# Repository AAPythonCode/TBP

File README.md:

# TBP (Tennis Ball Picker)

Hey!

Check out my JOURNALS.MD [here](https://github.com/AAPythonCode/TBP/blob/main/JOURNALS.md)

It's summer break, and I want to create something cool! Since I play tennis on a daily basis, I thought of creating something related to it. Therefore, I thought of creating a tennis ball picker that could collect tennis balls for the user, without collecting other players'.

I brainstormed many ideas, but in the end I thought of using cones on each of the four corners of the court to track the bot. Each cone would have a DWM1000 and a ESP32-WROOM-32, a low-cost programmable chip. The bot would also have the same, slightly modified board, which would use the distance data from each of the cones to find where it would be in relation to them.

Here's a drawing I made (painfully, my hand was shaking lol, did this on a phone):

# Bill of Materials (BOM)

### LCSC BOM:
| # | LCSC Part # | MPN | Manufacturer | Package | Quantity | Description |
|---:|-------------|-----|--------------|---------|---------:|-------------|
| 1 | C5241969 | DW1000-I-TR13 | Qorvo | QFN-48 (6×6 mm) | 5 | RF Transceiver IC, 3.244–6.999 GHz, 6.8 Mbps, −107 dBm, 2.8–3.6 V |
| 2 | C2907044 | FRC0603F5101TS | FOJAN | 0603 | 100 | 5.1 kΩ ±1%, 100 mW Thick Film Resistor |
| 3 | C717453 | S8050 | LGE | TO-92 | 20 | NPN BJT Transistor, 25 V, 500 mA, 150 MHz |
| 4 | C19273151 | YLED0603G | YONGYUTAI | 0603 | 100 | Emerald Green Indicator LED, 2.7–3.2 V |
| 5 | C141517 | TB6612FNG,C,8,EL | Toshiba | SSOP-24 | 1 | Dual H-Bridge Motor Driver |
| 6 | C695629 | DB301V-3.5-2P-GN-S | DORABO | Through Hole, 3.5 mm Pitch | 5 | 2-Position Wire-to-Board Terminal Block |
| 7 | C91606 | GRM188R61E106MA73D | Murata | 0603 | 5 | 10 µF ±20%, 25 V X5R Ceramic Capacitor |
| 8 | C2762594 | CL10A226MO7JZNC | Samsung Electro-Mechanics | 0603 | 5 | 22 µF ±20%, 16 V X5R Ceramic Capacitor |
| 9 | C207830 | SLO0420H4R7MTT | Sunltech | 4.2 × 4.2 mm SMD | 5 | 4.7 µH Molded Inductor, 2.2 A, 84 mΩ |
| 10 | C1590 | CL10B104KA8NNNC | Samsung Electro-Mechanics | 0603 | 50 | 100 nF ±10%, 25 V X7R Ceramic Capacitor |
| 11 | C98220 | RC0603FR-0710KL | YAGEO | 0603 | 100 | 10 kΩ ±1%, 100 mW Thick Film Resistor |
| 12 | C328062 | ESP32-WROOM-32U-N4 | Espressif | SMD, 19.2 × 18 mm | 5 | ESP32-WROOM-32U Wi-Fi/Bluetooth Module (External Antenna) |

## BOM For Everything Else:
| Product | Price | Manufacturer | Quantity | Link |
|---------|-------|--------------|----------|------|
Battery For Bot | $8.24 | AliExpress | 1 | [Link](https://www.aliexpress.us/item/3256811572811807.html?spm=a2g0o.detail.0.0.241ee2aYe2aY9A&mp=1&pdp_npi=6%40dis%21USD%21USD+31.69%21USD+8.20%21%21USD+8.20%21%21%21%40210327ef17836526403843839e1164%2112000056452625915%21ct%21US%21-1%21%211%210%21&_gl=1*mowjt7*_gcl_au*MTM5NjU0MTYyNC4xNzgyMTg1MjIw*_ga*OTg3MTQ2MjQ4LjE3ODM2NDk2ODY.*_ga_VED1YSGNC7*czE3ODM2NTE3ODgkbzIkZzEkdDE3ODM2NTI2MTckajU5JGwwJGgw&gatewayAdapt=glo2usa)
Battery For Cone | $3.67 | AliExpress | 4 | [Link](https://www.aliexpress.us/item/3256807641231334.html?spm=a2g0o.cart.0.0.677e38dazvj0aC&mp=1&pdp_npi=6%40dis%21USD%21USD+4.71%21USD+3.67%21%21USD+3.67%21%21%21%40210327ef17836529897426402e1164%2112000042353906286%21ct%21US%21-1%21%214%210%21&_gl=1*rah6qg*_gcl_au*MTM5NjU0MTYyNC4xNzgyMTg1MjIw*_ga*OTg3MTQ2MjQ4LjE3ODM2NDk2ODY.*_ga_VED1YSGNC7*czE3ODM2NTE3ODgkbzIkZzEkdDE3ODM2NTI5ODUkajQwJGwwJGgw&gatewayAdapt=glo2usa)
Caster Wheel (1 inch) | $6.89 | Amazon | 1 | [Link](https://www.amazon.com/Suiwotin-Casters-Replacement-Furniture-Cabinet/dp/B0C6JM7R2C/ref=sr_1_1?crid=G9WRSFY5IU30&dib=eyJ2IjoiMSJ9.7-JBT1HsoIndO6Nb_8mkSWVhn_iG1l5bbaN72kEroFq0E59IKfvyAlzAbGhL28Qy0klFiTsaZ9NMhDen2mC3Amcu-PpbKVTANfx0Uxh-y3oR3J0IiuYsMEy8AlGZf1hDu7_Nkn3xwIBqfYD3LpzfmKYA78j-cPIgqK75zkbXJZtpSlZKJ1o28_MMSl6raOjAua3VqijRvSrvi3kahNN8uuCBq-4MeWqScNZLNkaJBLk.mjZqq4LFhEt1wzEfHjUGeLU96UFfIbHFmp24r8qmJlg&dib_tag=se&keywords=caster%2Bwheel%2B2inch%2Bfor%2Bfurniture%2Bplate%2Bmount%2B2%2Bpcs&nsdOptOutParam=true&qid=1783467828&refinements=p_36%3A-800&rnid=2661611011&sprefix=caster%2Bwheel%2B2inch%2Bfor%2Bfurniture%2Bplate%2Bmount%2B2%2Bpc%2Caps%2C195&sr=8-1&th=1)
Wheels | $8.99 | AliExpress | 1 | [Link](https://www.amazon.com/gp/product/B0C6JQ3SDV/ref=ox_sc_act_title_2?smid=A22NPL1KB8AOV0&psc=1)
Motors | $4.34 | Amazon | 4 | [Link](https://www.amazon.com/gp/product/B0GXY1Y1XM/ref=ox_sc_act_title_2?smid=A3PMRUDTUKMNJ1&psc=1&s=bazaar)
DWM1000 | $0.80 | Alibaba | 5 | [Link](https://www.alibaba.com/product-detail/Electronic-components-integrated-circuits-semiconductor-New_1601393696798.html?spm=a2756.trade-order-standard.0.0.e08265aaEoXY4F)
### GRAND TOTAL: $349.28

# Images

Now for some images! Take it all in... :)

## The Schematic

## The LED

## The DWM1000 + ESP32-WROOM-32 (from left to right, respectively.)

## Transistors

## The Full Bot PCB

## The Bot PCB in 3D

## The Full Cone PCB

## The Cone PCB in 3D

## The Fully Assembled Bot

## The Fully Assembled Cone

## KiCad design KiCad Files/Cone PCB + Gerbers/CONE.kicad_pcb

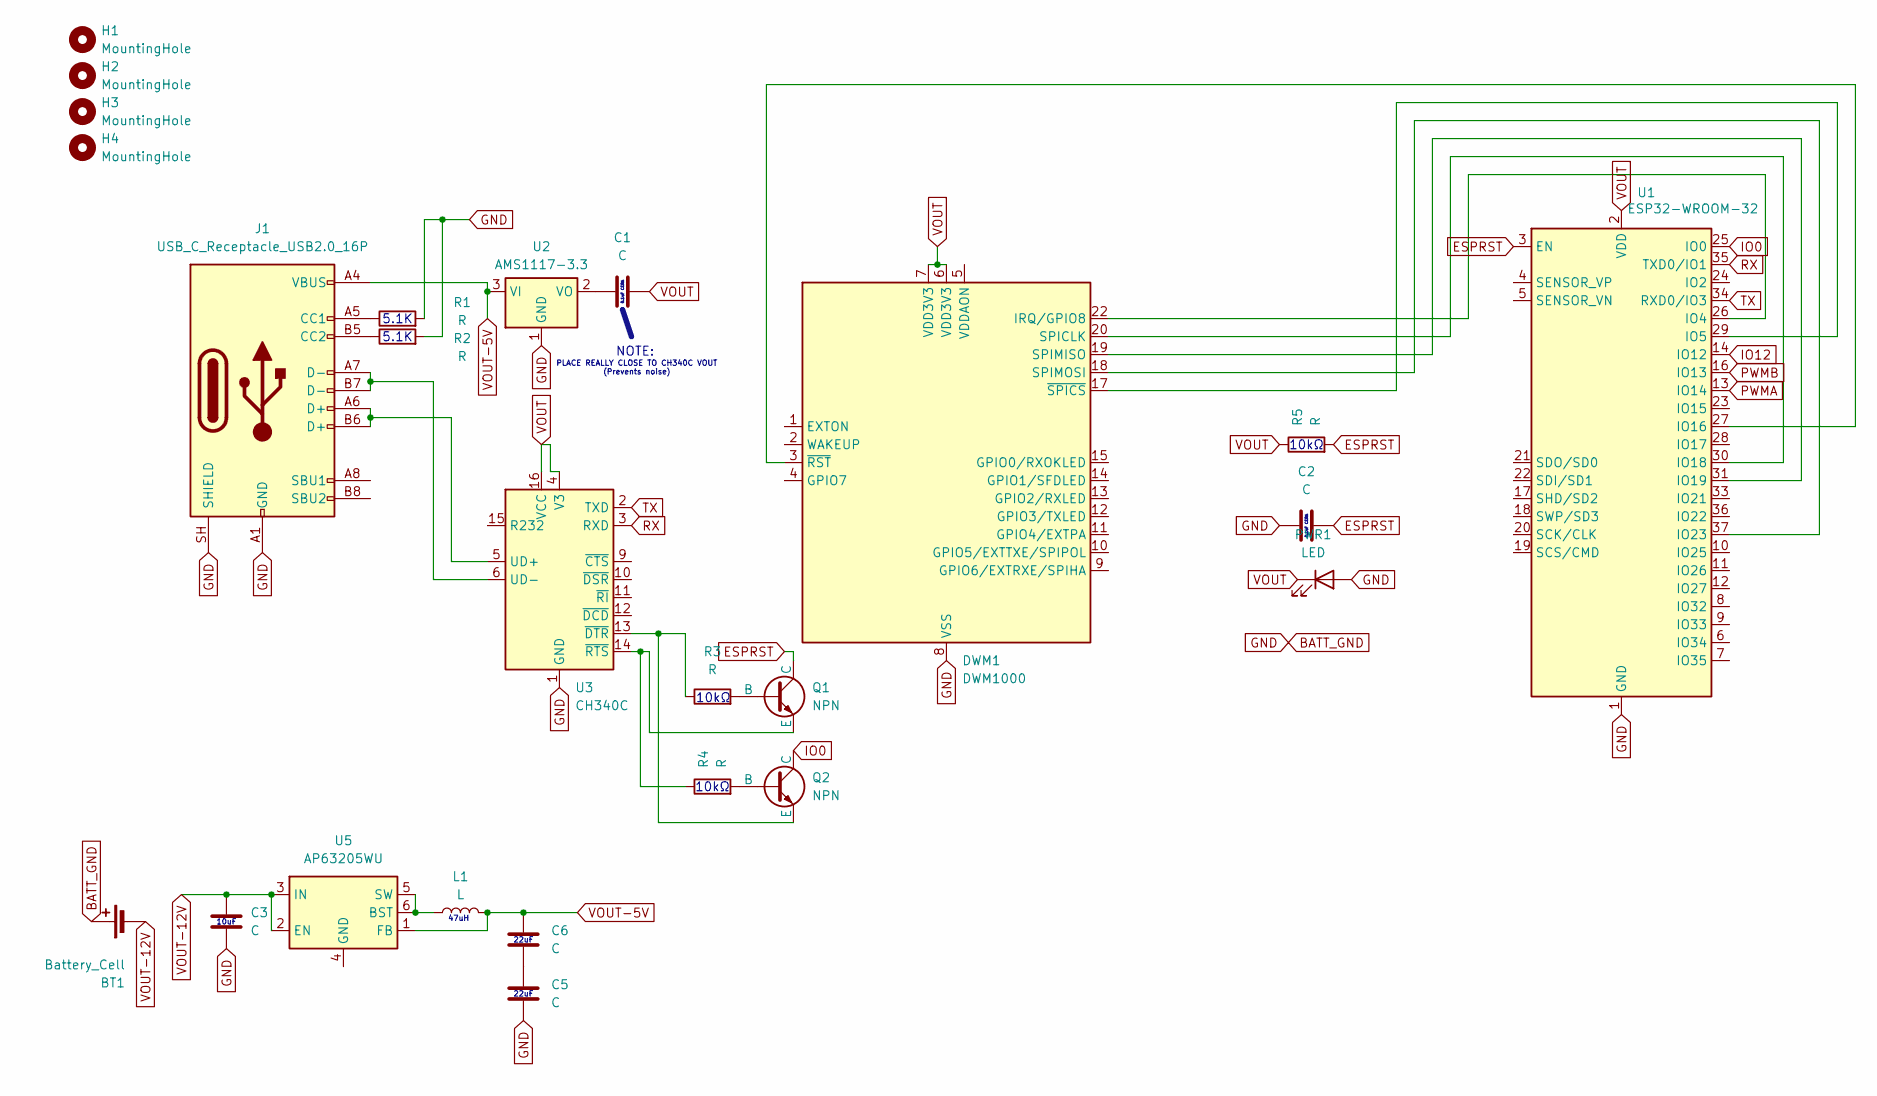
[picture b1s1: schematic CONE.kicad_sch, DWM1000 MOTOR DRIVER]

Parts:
BT1: Battery_Cell; PinSocket_1x02_P2.54mm_Vertical
C1, C2: C; C_0603_1608Metric
C3, C5, C6: C; C_0201_0603Metric
DWM1: DWM1000
H1, H2, H3, H4: MountingHole; MountingHole_2.5mm
J1: USB_C_Receptacle_USB2.0_16P; USB_C_Receptacle_HRO_TYPE-C-31-M-12
L1: L; IND_SRP4020TA-100M
PWR1: LED; LED_0603_1608Metric
Q1, Q2: NPN; TO-92
R1, R2, R3, R4, R5: R; R_0603_1608Metric
U1: ESP32-WROOM-32
U2: AMS1117-3.3; SOT-223-3_TabPin2
U3: CH340C; SOIC-16_3.9x9.9mm_P1.27mm
U5: AP63205WU; TSOT-23-6

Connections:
BATT_GND: BT1.1 (+), C2.1, C3.2, C5.2, DWM1.8 (VSS), DWM1.16 (VSS), DWM1.21 (VSS), DWM1.23 (VSS), DWM1.24 (VSS), J1.A1 (GND), J1.A12 (GND), J1.B1 (GND), J1.B12 (GND), J1.SH (SHIELD), PWR1.2 (A), R1.2, R2.2, U1.1 (GND), U1.15 (GND), U1.38 (GND), U1.39 (GND), U2.1 (GND), U3.1 (GND)
ESPRST: C2.2, Q1.1 (C), R5.2, U1.3 (EN)
IO0: Q2.1 (C), U1.25 (IO0)
IO12: U1.14 (IO12)
unnamed: C5.1, C6.2
unnamed: DWM1.22 (IRQ/GPIO8), U1.26 (IO4)
unnamed: DWM1.20 (SPICLK), U1.30 (IO18)
unnamed: DWM1.19 (SPIMISO), U1.31 (IO19)
unnamed: DWM1.18 (SPIMOSI), U1.37 (IO23)
unnamed: DWM1.3 (~RST), U1.27 (IO16)
unnamed: DWM1.17 (~SPICS), U1.29 (IO5)
unnamed: J1.A5 (CC1), R1.1
unnamed: J1.B5 (CC2), R2.1
unnamed: Q1.2 (B), R3.2
unnamed: Q1.3 (E), R4.1, U3.14 (~RTS)
unnamed: Q2.2 (B), R4.2
unnamed: Q2.3 (E), R3.1, U3.13 (~DTR)
unnamed: C1.1, U2.2 (VO)
unnamed: J1.A6 (D+), J1.B6 (D+), U3.5 (UD+)
unnamed: J1.A7 (D-), J1.B7 (D-), U3.6 (UD-)
unnamed: L1.1, U5.5 (SW), U5.6 (BST)
PWMA: U1.13 (IO14)
PWMB: U1.16 (IO13)
RX: U1.35 (TXD0/IO1), U3.3 (RXD)
TX: U1.34 (RXD0/IO3), U3.2 (TXD)
VOUT: C1.2, DWM1.6 (VDD3V3), DWM1.7 (VDD3V3), PWR1.1 (K), R5.1, U1.2 (VDD), U3.4 (V3), U3.16 (VCC)
VOUT-5V: C6.1, J1.A4 (VBUS), J1.A9 (VBUS), J1.B4 (VBUS), J1.B9 (VBUS), L1.2, U2.3 (VI), U5.1 (FB)
VOUT-12V: BT1.2 (-), C3.1, U5.2 (EN), U5.3 (IN)

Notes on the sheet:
5.1K
0.1uF CERA
10kΩ
47uH
NOTE:
22uF
PLACE REALLY CLOSE TO CH340C VOUT (Prevents noise)
10uF

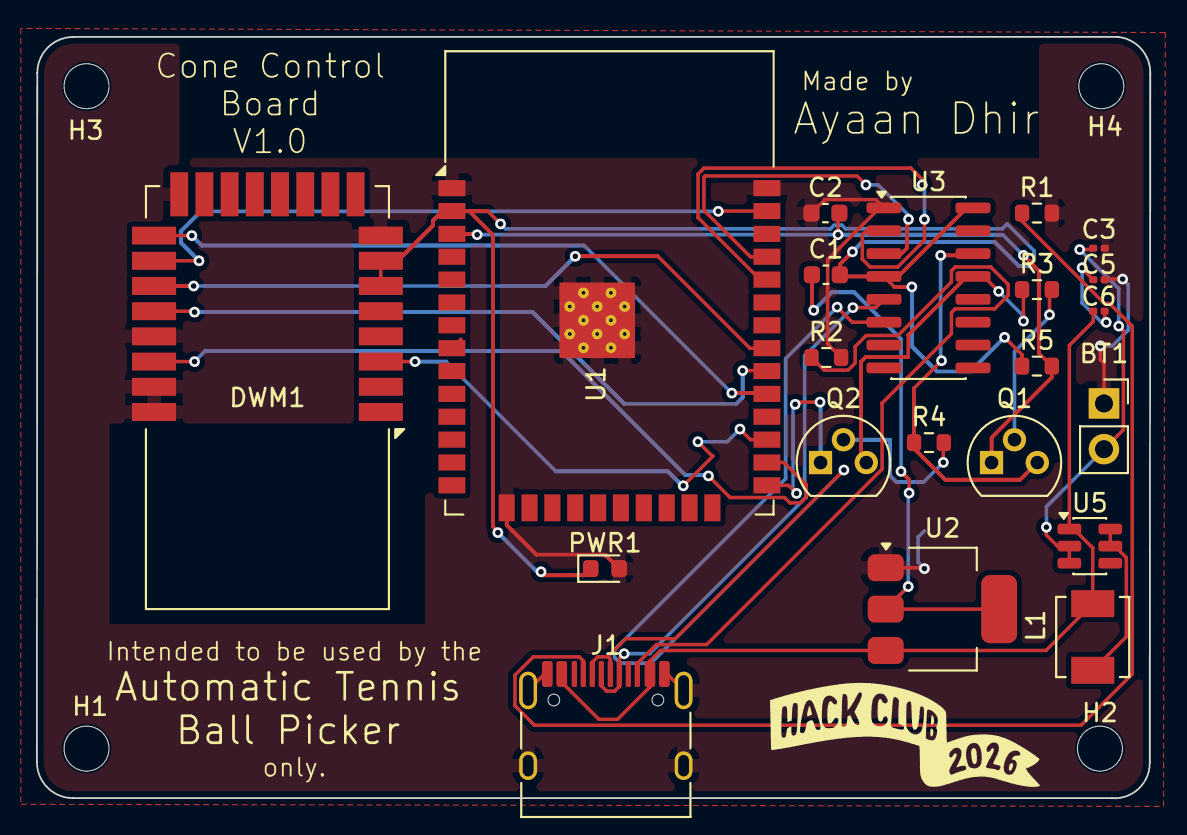
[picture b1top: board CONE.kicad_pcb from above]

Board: 2 copper layers, 61.9 x 42.3 mm, 25 parts (0 on the bottom side), 25 nets.

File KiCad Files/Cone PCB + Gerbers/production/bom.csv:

Designator,Footprint,Quantity,Value,LCSC Part #
BT1,PinSocket_1x02_P2.54mm_Vertical,1,Battery_Cell,
"C1, C2",0603,2,C,
"C3, C5, C6",0201,3,C,
DWM1,DWM1000,1,DWM1000,
J1,USB_C_Receptacle_HRO_TYPE-C-31-M-12,1,USB_C_Receptacle_USB2.0_16P,
L1,IND_SRP4020TA-100M,1,L,
PWR1,0603,1,LED,
"Q1, Q2",TO-92,2,NPN,
"R1, R2, R3, R4, R5",0603,5,R,
U1,ESP32-WROOM-32,1,ESP32-WROOM-32,
U2,SOT-223-3_TabPin2,1,AMS1117-3.3,
U3,SOIC-16_3.9x9.9mm_P1.27mm,1,CH340C,
U5,TSOT-23-6,1,AP63205WU,

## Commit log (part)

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2026-06-28 add folders
